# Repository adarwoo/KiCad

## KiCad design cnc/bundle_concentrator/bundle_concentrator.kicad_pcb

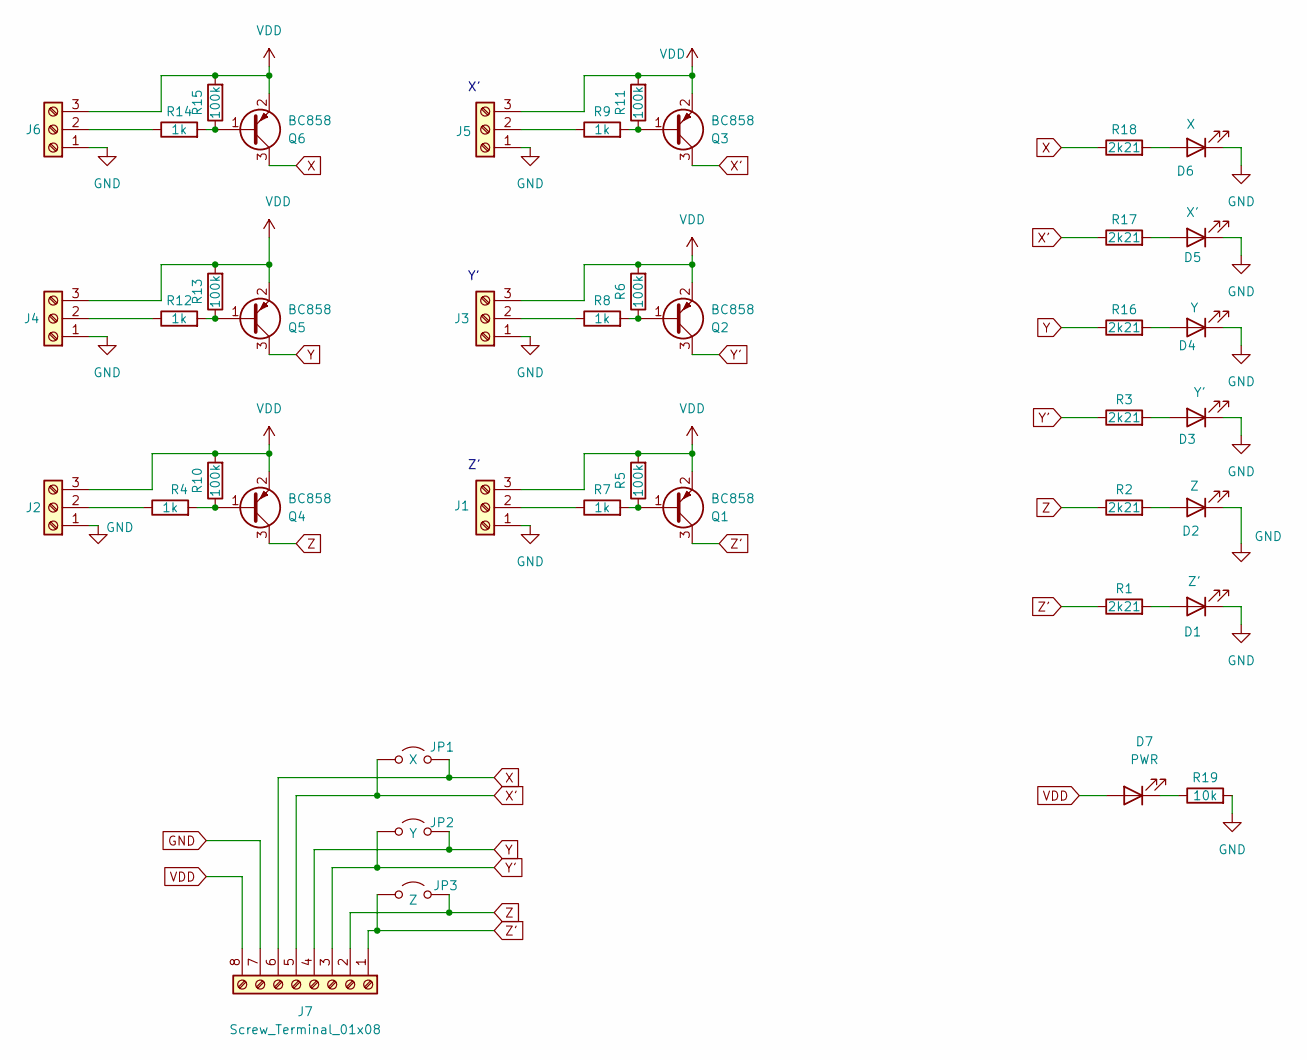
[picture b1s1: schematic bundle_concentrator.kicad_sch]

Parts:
D1: Z'; LED_D3.0mm
D2: Z; LED_D3.0mm
D3: Y'; LED_D3.0mm
D4: Y; LED_D3.0mm
D5: X'; LED_D3.0mm
D6: X; LED_D3.0mm
D7: PWR; LED_D3.0mm
J1: Z'; PhoenixContact_MCV_1,5_3-G-3.5_1x03_P3.50mm_Vertical
J2: Z; PhoenixContact_MCV_1,5_3-G-3.5_1x03_P3.50mm_Vertical
J3: Y'; PhoenixContact_MCV_1,5_3-G-3.5_1x03_P3.50mm_Vertical
J4: Y; PhoenixContact_MCV_1,5_3-G-3.5_1x03_P3.50mm_Vertical
J5: X'; PhoenixContact_MCV_1,5_3-G-3.5_1x03_P3.50mm_Vertical
J6: XX; PhoenixContact_MCV_1,5_3-G-3.5_1x03_P3.50mm_Vertical
J7: Screw_Terminal_01x08; PhoenixContact_MCV_1,5_8-G-3.81_1x08_P3.81mm_Vertical
JP1: X; PinHeader_1x02_P2.54mm_Vertical
JP2: Y; PinHeader_1x02_P2.54mm_Vertical
JP3: Z; PinHeader_1x02_P2.54mm_Vertical
Q1, Q2, Q3, Q4, Q5, Q6: BC858; SOT-23
R1, R2, R3, R16, R17, R18: 2k21; R_1206_3216Metric_Pad1.30x1.75mm_HandSolder
R4, R7, R8, R9, R12, R14: 1k; R_1206_3216Metric_Pad1.30x1.75mm_HandSolder
R5, R6, R10, R11, R13, R15: 100k; R_1206_3216Metric_Pad1.30x1.75mm_HandSolder
R19: 10k; R_1206_3216Metric_Pad1.30x1.75mm_HandSolder

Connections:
GND: D1.1 (K), D2.1 (K), D3.1 (K), D4.1 (K), D5.1 (K), D6.1 (K), J1.1, J2.1, J3.1, J4.1, J5.1, J6.1, J7.7, R19.2
unnamed: D1.2 (A), R1.2
unnamed: D2.2 (A), R2.2
unnamed: D3.2 (A), R3.2
unnamed: D4.2 (A), R16.2
unnamed: D5.2 (A), R17.2
unnamed: D6.2 (A), R18.2
unnamed: D7.1 (K), R19.1
unnamed: J1.2, R7.1
unnamed: J2.2, R4.1
unnamed: J3.2, R8.1
unnamed: J4.2, R12.1
unnamed: J5.2, R9.1
unnamed: J6.2, R14.1
unnamed: Q1.1 (B), R5.1, R7.2
unnamed: Q2.1 (B), R6.1, R8.2
unnamed: Q3.1 (B), R9.2, R11.1
unnamed: Q4.1 (B), R4.2, R10.1
unnamed: Q5.1 (B), R12.2, R13.1
unnamed: Q6.1 (B), R14.2, R15.1
VDD: D7.2 (A), J1.3, J2.3, J3.3, J4.3, J5.3, J6.3, J7.8, Q1.2 (E), Q2.2 (E), Q3.2 (E), Q4.2 (E), Q5.2 (E), Q6.2 (E), R5.2, R6.2, R10.2, R11.2, R13.2, R15.2
X: J7.6, JP1.2 (B), Q6.3 (C), R18.1
X': J7.5, JP1.1 (A), Q3.3 (C), R17.1
Y: J7.4, JP2.2 (B), Q5.3 (C), R16.1
Y': J7.3, JP2.1 (A), Q2.3 (C), R3.1
Z: J7.2, JP3.2 (B), Q4.3 (C), R2.1
Z': J7.1, JP3.1 (A), Q1.3 (C), R1.1

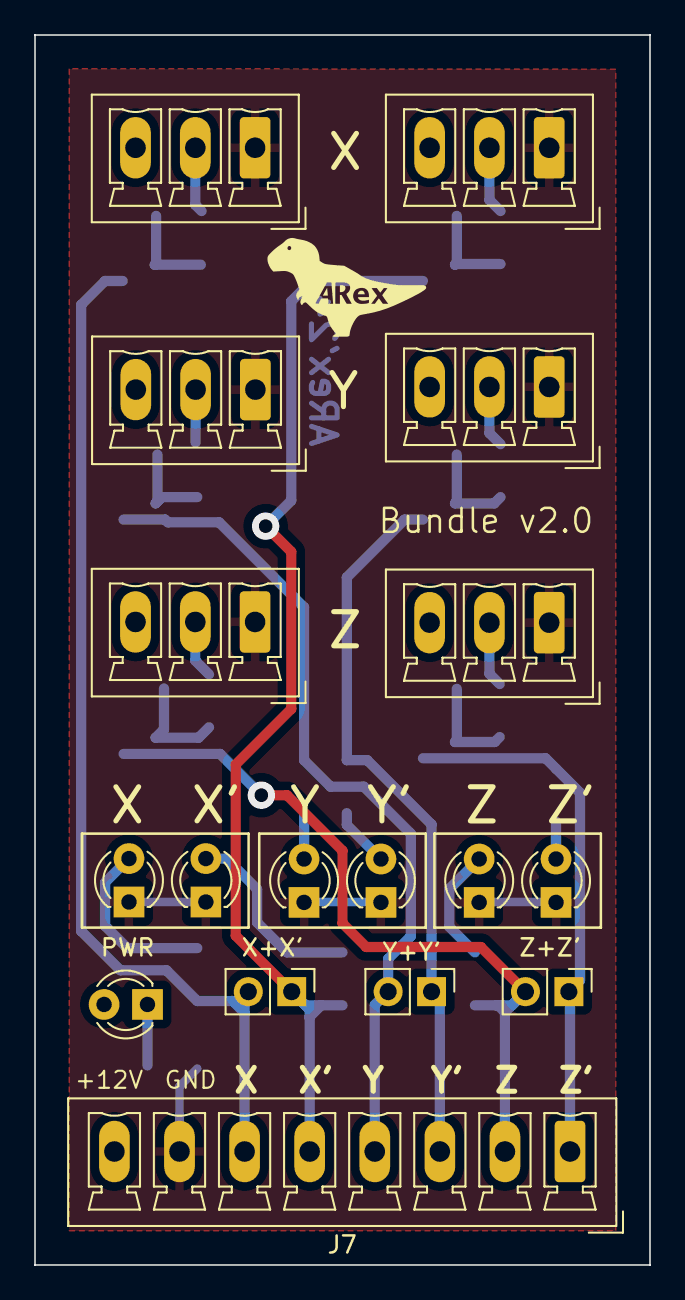
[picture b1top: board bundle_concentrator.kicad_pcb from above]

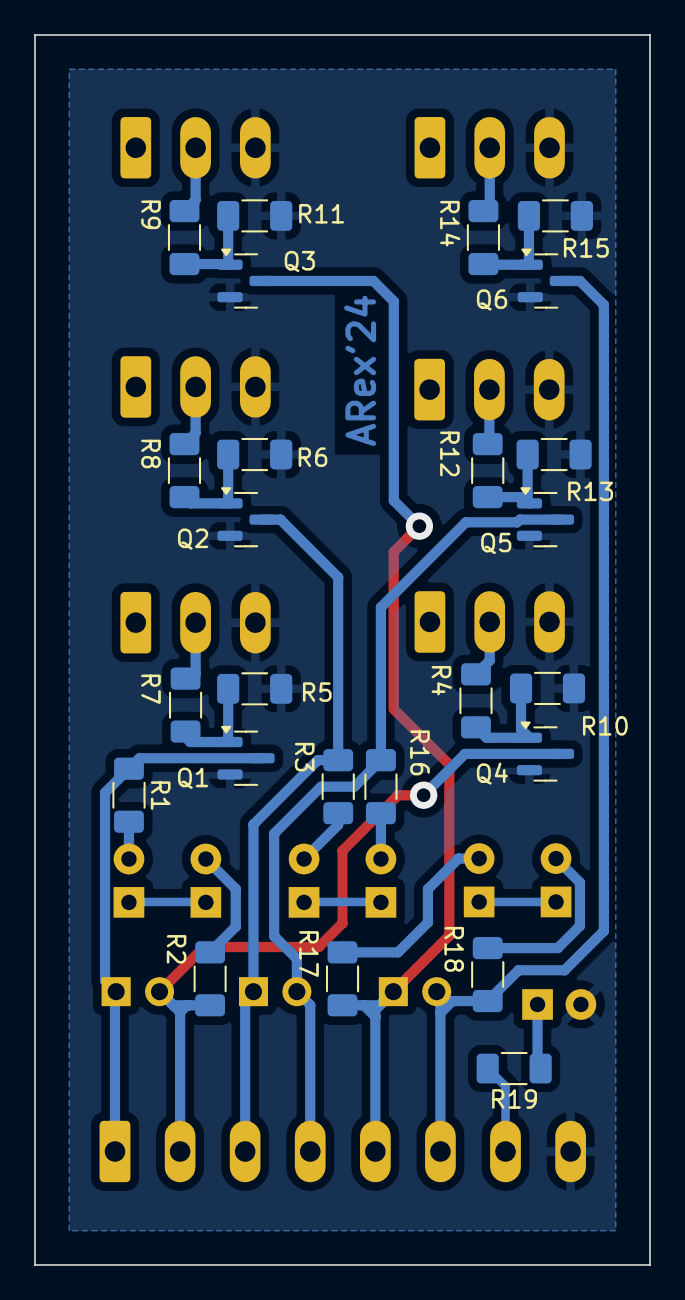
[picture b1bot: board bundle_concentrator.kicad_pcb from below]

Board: 2 copper layers, 36.0 x 72.0 mm, 42 parts (25 on the bottom side), 27 nets.

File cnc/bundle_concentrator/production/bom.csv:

Designator,Footprint,Quantity,Value,LCSC Part #
D1,LED_D3.0mm,1,Z',
D2,LED_D3.0mm,1,Z,
D3,LED_D3.0mm,1,Y',
D4,LED_D3.0mm,1,Y,
D5,LED_D3.0mm,1,X',
D6,LED_D3.0mm,1,X,
D7,LED_D3.0mm,1,PWR,
J1,"PhoenixContact_MCV_1,5_3-G-3.5_1x03_P3.50mm_Vertical",1,Z',
J2,"PhoenixContact_MCV_1,5_3-G-3.5_1x03_P3.50mm_Vertical",1,Z,
J3,"PhoenixContact_MCV_1,5_3-G-3.5_1x03_P3.50mm_Vertical",1,Y',
J4,"PhoenixContact_MCV_1,5_3-G-3.5_1x03_P3.50mm_Vertical",1,Y,
J5,"PhoenixContact_MCV_1,5_3-G-3.5_1x03_P3.50mm_Vertical",1,X',
J6,"PhoenixContact_MCV_1,5_3-G-3.5_1x03_P3.50mm_Vertical",1,XX,
J7,"PhoenixContact_MCV_1,5_8-G-3.81_1x08_P3.81mm_Vertical",1,Screw_Terminal_01x08,
JP1,PinHeader_1x02_P2.54mm_Vertical,1,X,
JP2,PinHeader_1x02_P2.54mm_Vertical,1,Y,
JP3,PinHeader_1x02_P2.54mm_Vertical,1,Z,
"Q1, Q2, Q3, Q4, Q5, Q6",SOT-23,6,BC858,
"R1, R16, R17, R18, R19, R2, R3",1206,7,10k,
"R10, R11, R13, R15, R5, R6",1206,6,100k,
"R12, R14, R4, R7, R8, R9",1206,6,1k,

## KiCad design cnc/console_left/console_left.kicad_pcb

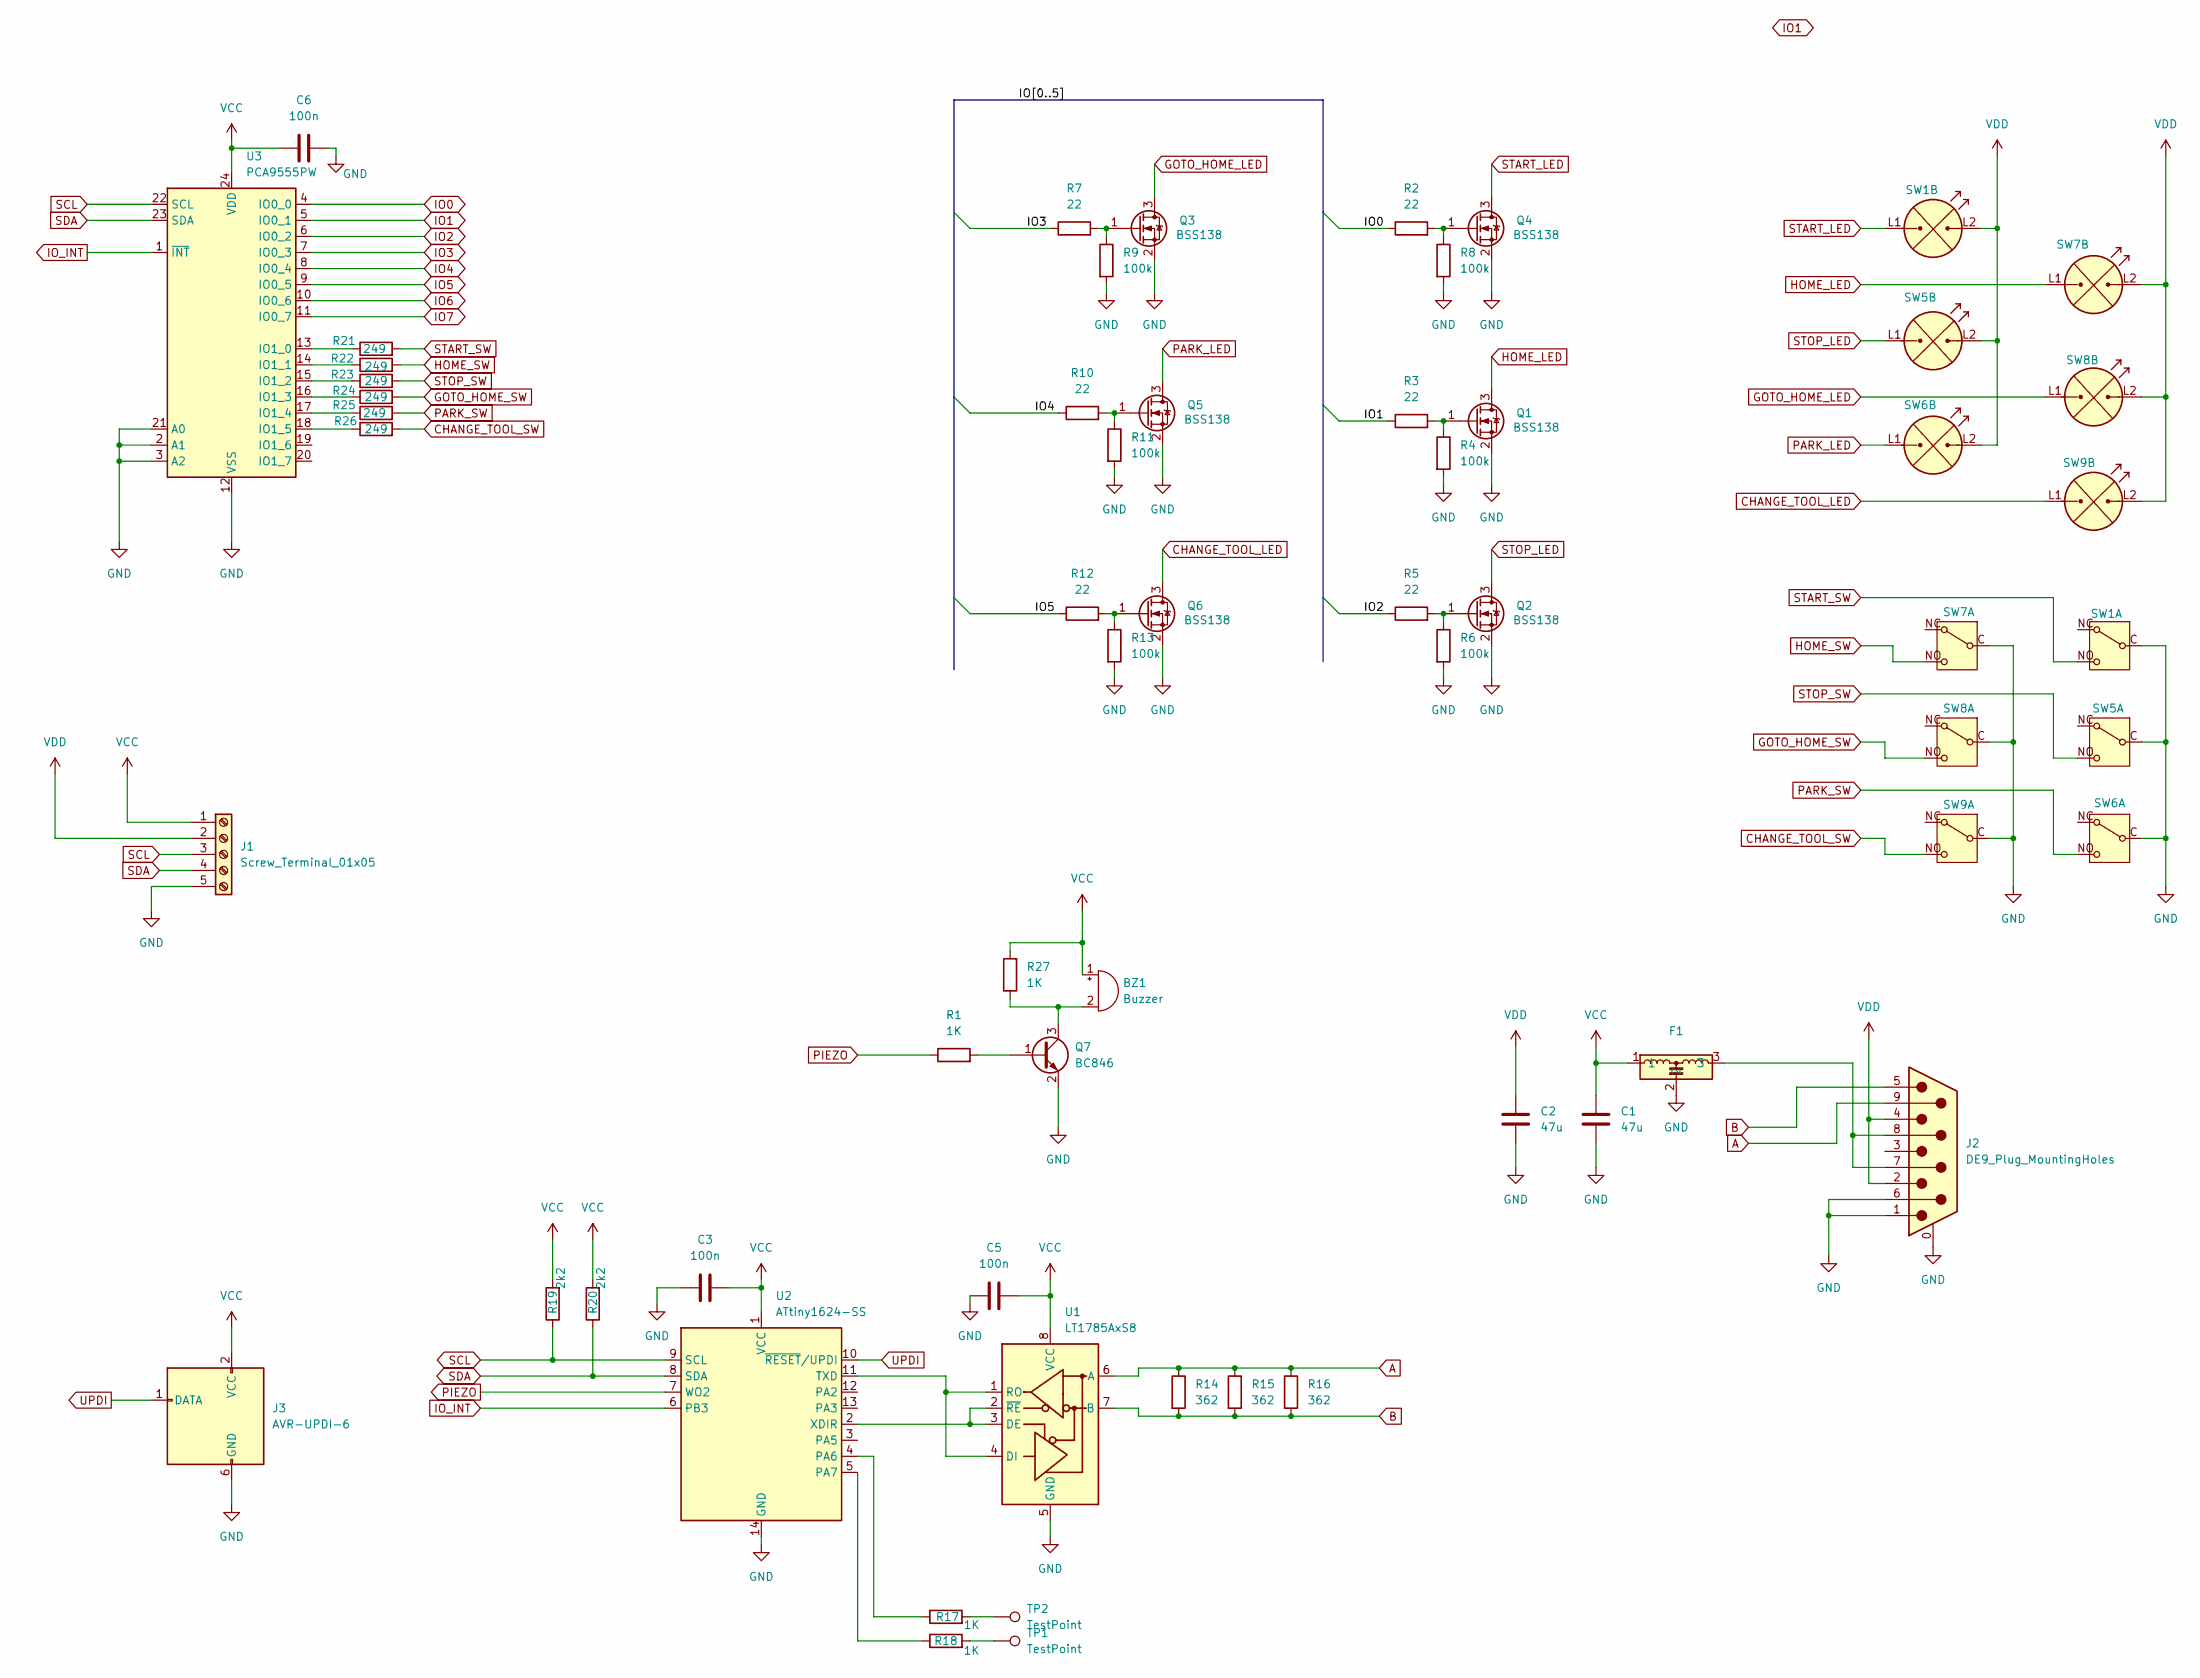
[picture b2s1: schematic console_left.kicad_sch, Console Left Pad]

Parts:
BZ1: Buzzer; Buzzer_Murata_PKLCS1212E
C1, C2: 47u; C_1210_3225Metric_Pad1.33x2.70mm_HandSolder
C3, C5, C6: 100n; C_0603_1608Metric_Pad1.08x0.95mm_HandSolder
F1: Murata_NFM61R
J1: Screw_Terminal_01x05; Molex_KK-254_AE-6410-05A_1x05_P2.54mm_Vertical
J2: DE9_Plug_MountingHoles; DSUB-9_Female_EdgeMount_P2.77mm
J3: AVR-UPDI-6; PinHeader_2x03_P2.54mm_Vertical
Q1, Q2, Q3, Q4, Q5, Q6: BSS138; SOT-23
Q7: BC846; SOT-23
R1, R17, R18, R27: 1K; R_1206_3216Metric_Pad1.30x1.75mm_HandSolder
R2, R3, R5, R7, R10, R12: 22; R_1206_3216Metric_Pad1.30x1.75mm_HandSolder
R4, R6, R8, R9, R11, R13: 100k; R_1206_3216Metric_Pad1.30x1.75mm_HandSolder
R14, R15, R16: 362; R_1206_3216Metric_Pad1.30x1.75mm_HandSolder
R19, R20: 2k2; R_1206_3216Metric_Pad1.30x1.75mm_HandSolder
R21, R22, R23, R24, R25, R26: 249; R_1206_3216Metric_Pad1.30x1.75mm_HandSolder
SW1, SW5, SW6, SW7, SW8, SW9: PUSH_STDP_LED
TP1, TP2: TestPoint; TestPoint_Loop_D1.80mm_Drill1.0mm_Beaded
U1: LT1785AxS8; SOIC-8_3.9x4.9mm_P1.27mm
U2: ATtiny1624-SS; SOIC-14_3.9x8.7mm_P1.27mm
U3: PCA9555PW; TSSOP-24_4.4x7.8mm_P0.65mm

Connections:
A: J2.9, R14.1, R15.1, R16.1, U1.6 (A)
B: J2.5, R14.2, R15.2, R16.2, U1.7 (B)
CHANGE_TOOL_LED: Q6.3 (D), SW9.L1 (AK)
CHANGE_TOOL_SW: R26.2, SW9.NO
GND: C1.2, C2.2, C3.1, C5.1, C6.2, F1.2, J1.5, J2.0 (PAD), J2.1, J2.6, J3.6 (GND), Q1.2 (S), Q2.2 (S), Q3.2 (S), Q4.2 (S), Q5.2 (S), Q6.2 (S), Q7.2 (E), R4.2, R6.2, R8.2, R9.2, R11.2, R13.2, SW1.C, SW5.C, SW6.C, SW7.C, SW8.C, SW9.C, U1.5 (GND), U2.14 (GND), U3.2 (A1), U3.3 (A2), U3.12 (VSS), U3.21 (A0)
GOTO_HOME_LED: Q3.3 (D), SW8.L1 (AK)
GOTO_HOME_SW: R24.2, SW8.NO
HOME_LED: Q1.3 (D), SW7.L1 (AK)
HOME_SW: R22.2, SW7.NO
IO0: R2.1, U3.4 (IO0_0)
IO1: R3.1, U3.5 (IO0_1)
IO2: R5.1, U3.6 (IO0_2)
IO3: R7.1, U3.7 (IO0_3)
IO4: R10.1, U3.8 (IO0_4)
IO5: R12.1, U3.9 (IO0_5)
IO6: U3.10 (IO0_6)
IO7: U3.11 (IO0_7)
IO_INT: U2.6 (PB3), U3.1 (~INT)
unnamed: BZ1.2 (-), Q7.3 (C), R27.1
unnamed: F1.3, J2.7, J2.8
unnamed: Q1.1 (G), R3.2, R4.1
unnamed: Q2.1 (G), R5.2, R6.1
unnamed: Q3.1 (G), R7.2, R9.1
unnamed: Q4.1 (G), R2.2, R8.1
unnamed: Q5.1 (G), R10.2, R11.1
unnamed: Q6.1 (G), R12.2, R13.1
unnamed: Q7.1 (B), R1.2
unnamed: R17.2, TP2.1
unnamed: R18.2, TP1.1
unnamed: U1.2 (~RE), U1.3 (DE), U2.2 (XDIR)
unnamed: U1.1 (RO), U1.4 (DI), U2.11 (TXD)
unnamed: R17.1, U2.4 (PA6)
unnamed: R18.1, U2.5 (PA7)
unnamed: R21.1, U3.13 (IO1_0)
unnamed: R22.1, U3.14 (IO1_1)
unnamed: R23.1, U3.15 (IO1_2)
unnamed: R24.1, U3.16 (IO1_3)
unnamed: R25.1, U3.17 (IO1_4)
unnamed: R26.1, U3.18 (IO1_5)
PARK_LED: Q5.3 (D), SW6.L1 (AK)
PARK_SW: R25.2, SW6.NO
PIEZO: R1.1, U2.7 (WO2)
SCL: J1.3, R19.1, U2.9 (SCL), U3.22 (SCL)
SDA: J1.4, R20.1, U2.8 (SDA), U3.23 (SDA)
START_LED: Q4.3 (D), SW1.L1 (AK)
START_SW: R21.2, SW1.NO
STOP_LED: Q2.3 (D), SW5.L1 (AK)
STOP_SW: R23.2, SW5.NO
UPDI: J3.1 (DATA), U2.10 (~RESET/UPDI)
VCC: BZ1.1 (+), C1.1, C3.2, C5.2, C6.1, F1.1, J1.1, J3.2 (VCC), R19.2, R20.2, R27.2, U1.8 (VCC), U2.1 (VCC), U3.24 (VDD)
VDD: C2.1, J1.2, J2.2, J2.4, SW1.L2 (KA), SW5.L2 (KA), SW6.L2 (KA), SW7.L2 (KA), SW8.L2 (KA), SW9.L2 (KA)

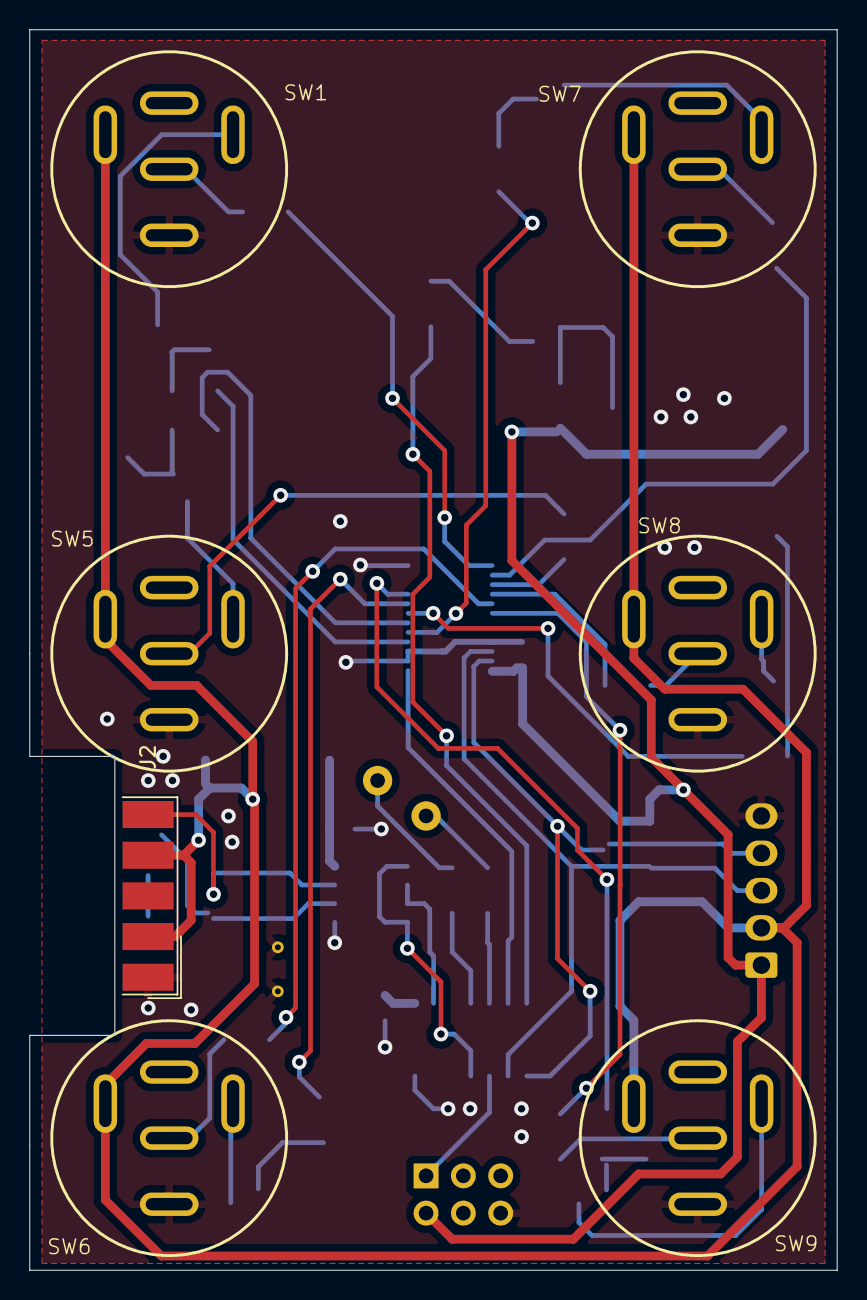
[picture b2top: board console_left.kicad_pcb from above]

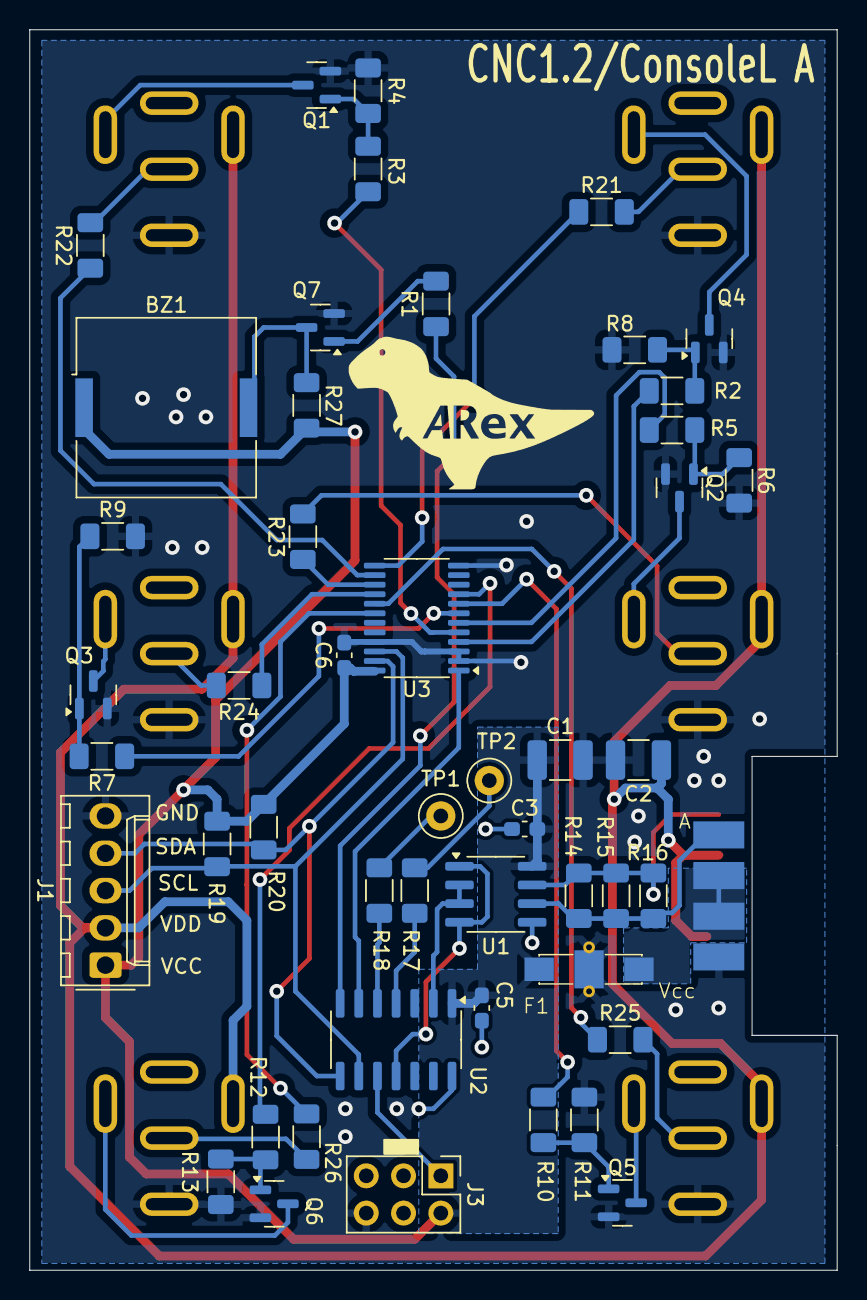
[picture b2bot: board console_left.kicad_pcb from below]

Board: 2 copper layers, 55.0 x 84.5 mm, 55 parts (48 on the bottom side), 49 nets.

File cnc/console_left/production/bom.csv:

Designator,Footprint,Quantity,Value,LCSC Part #
BZ1,Buzzer_Murata_PKLCS1212E,1,Buzzer,
"C1, C2",1210,2,47u,
"C3, C5, C6",0603,3,100n,
F1,Murata_NFM61R,1,~,
J1,Molex_KK-254_AE-6410-05A_1x05_P2.54mm_Vertical,1,Screw_Terminal_01x05,
J2,DSUB-9_Female_EdgeMount_P2.77mm,1,DE9_Plug_MountingHoles,
J3,PinHeader_2x03_P2.54mm_Vertical,1,AVR-UPDI-6,
"Q1, Q2, Q3, Q4, Q5, Q6",SOT-23,6,BSS138,
Q7,SOT-23,1,BC846,
"R1, R17, R18, R27",1206,4,1K,
"R10, R12, R2, R3, R5, R7",1206,6,22,
"R11, R13, R4, R6, R8, R9",1206,6,100k,
"R14, R15, R16",1206,3,362,
"R19, R20",1206,2,2k2,
"R21, R22, R23, R24, R25, R26",1206,6,332,
"SW1, SW5, SW6, SW7, SW8, SW9",PUSH_STDP_LED,6,~,
"TP1, TP2",TestPoint_Loop_D1.80mm_Drill1.0mm_Beaded,2,TestPoint,
U1,SOIC-8_3.9x4.9mm_P1.27mm,1,LT1785AxS8,
U2,SOIC-14_3.9x8.7mm_P1.27mm,1,ATtiny1624-SS,
U3,TSSOP-24_4.4x7.8mm_P0.65mm,1,PCA9555PW,

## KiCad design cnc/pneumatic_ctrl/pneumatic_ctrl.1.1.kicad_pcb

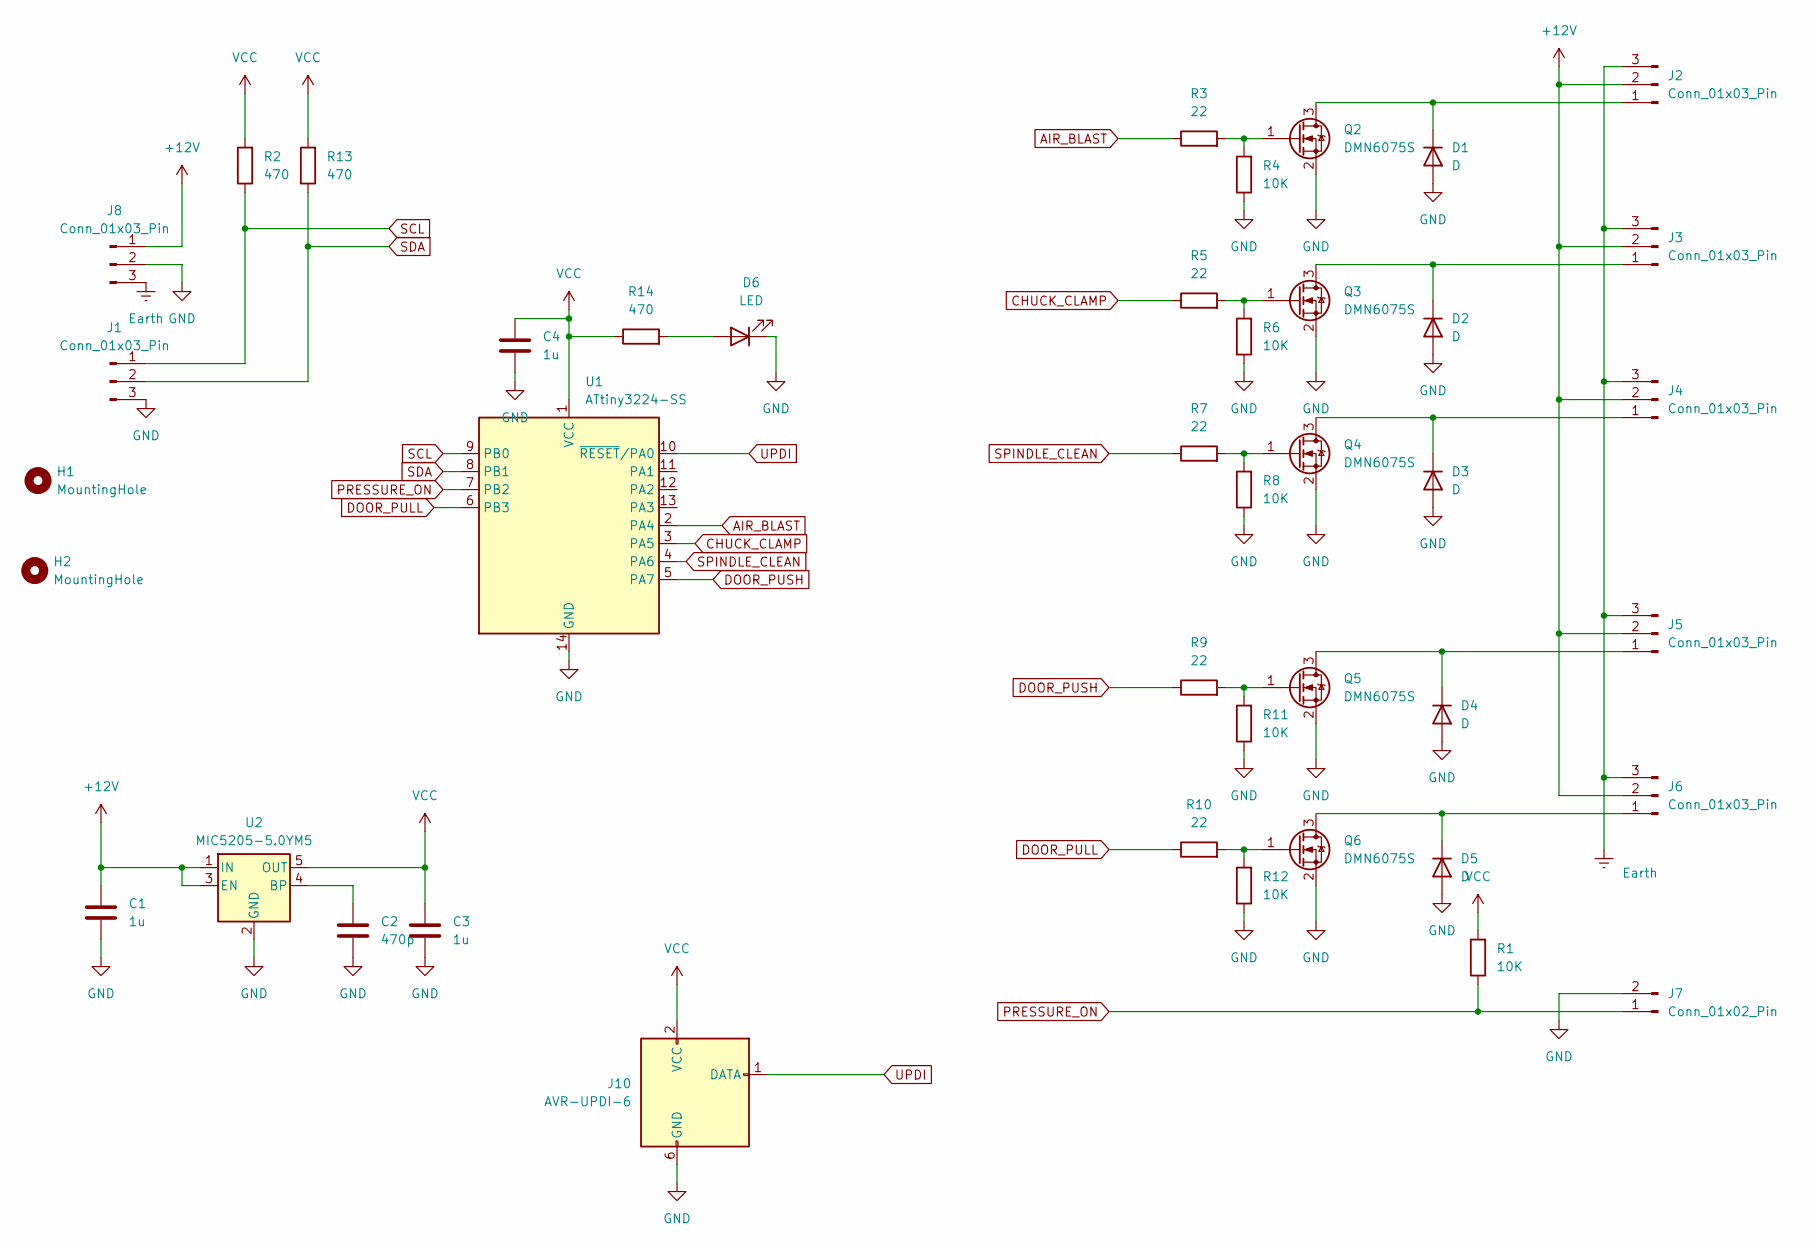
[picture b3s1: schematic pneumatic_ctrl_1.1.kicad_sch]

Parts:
C1, C3, C4: 1u; C_1206_3216Metric_Pad1.33x1.80mm_HandSolder
C2: 470p; C_0805_2012Metric_Pad1.18x1.45mm_HandSolder
D1, D2, D3, D4, D5: D; D_MicroSMP_AK
D6: LED; LED_D3.0mm
H1, H2: MountingHole; MountingHole_3.2mm_M3_DIN965
J1, J2, J3, J4, J5, J6, J8: Conn_01x03_Pin; PhoenixContact_MCV_1,5_3-G-3.81_1x03_P3.81mm_Vertical
J7: Conn_01x02_Pin; PhoenixContact_MCV_1,5_2-G-3.81_1x02_P3.81mm_Vertical
J10: AVR-UPDI-6; PinHeader_2x03_P2.54mm_Vertical
Q2, Q3, Q4, Q5, Q6: DMN6075S; SOT-23
R1, R4, R6, R8, R11, R12: 10K; R_1206_3216Metric_Pad1.30x1.75mm_HandSolder
R2, R13, R14: 470; R_1206_3216Metric_Pad1.30x1.75mm_HandSolder
R3, R5, R7, R9, R10: 22; R_1206_3216Metric_Pad1.30x1.75mm_HandSolder
U1: ATtiny3224-SS; SOIC-14_3.9x8.7mm_P1.27mm
U2: MIC5205-5.0YM5; SOT-23-5

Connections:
+12V: C1.1, J2.2, J3.2, J4.2, J5.2, J6.2, J8.1, U2.1 (IN), U2.3 (EN)
AIR_BLAST: R3.1, U1.2 (PA4)
CHUCK_CLAMP: R5.1, U1.3 (PA5)
DOOR_PULL: R10.1, U1.6 (PB3)
DOOR_PUSH: R9.1, U1.5 (PA7)
Earth: J2.3, J3.3, J4.3, J5.3, J6.3, J8.3
GND: C1.2, C2.2, C3.2, C4.2, D1.2 (A), D2.2 (A), D3.2 (A), D4.2 (A), D5.2 (A), D6.1 (K), J1.3, J7.2, J8.2, J10.6 (GND), Q2.2 (S), Q3.2 (S), Q4.2 (S), Q5.2 (S), Q6.2 (S), R4.1, R6.1, R8.1, R11.1, R12.1, U1.14 (GND), U2.2 (GND)
unnamed: D1.1 (K), J2.1, Q2.3 (D)
unnamed: D2.1 (K), J3.1, Q3.3 (D)
unnamed: D3.1 (K), J4.1, Q4.3 (D)
unnamed: D4.1 (K), J5.1, Q5.3 (D)
unnamed: D5.1 (K), J6.1, Q6.3 (D)
unnamed: D6.2 (A), R14.2
unnamed: Q2.1 (G), R3.2, R4.2
unnamed: Q3.1 (G), R5.2, R6.2
unnamed: Q4.1 (G), R7.2, R8.2
unnamed: Q5.1 (G), R9.2, R11.2
unnamed: Q6.1 (G), R10.2, R12.2
unnamed: C2.1, U2.4 (BP)
PRESSURE_ON: J7.1, R1.1, U1.7 (PB2)
SCL: J1.1, R2.1, U1.9 (PB0)
SDA: J1.2, R13.1, U1.8 (PB1)
SPINDLE_CLEAN: R7.1, U1.4 (PA6)
UPDI: J10.1 (DATA), U1.10 (~RESET/PA0)
VCC: C3.1, C4.1, J10.2 (VCC), R1.2, R2.2, R13.2, R14.1, U1.1 (VCC), U2.5 (OUT)

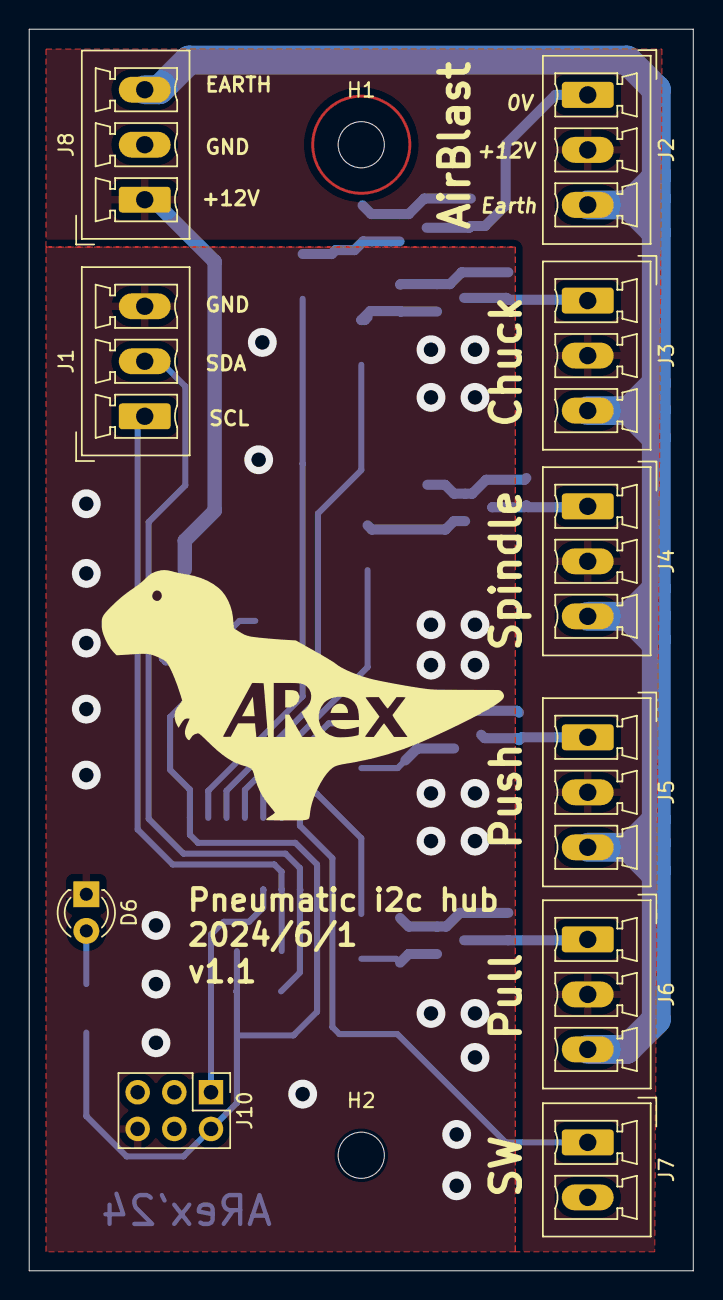
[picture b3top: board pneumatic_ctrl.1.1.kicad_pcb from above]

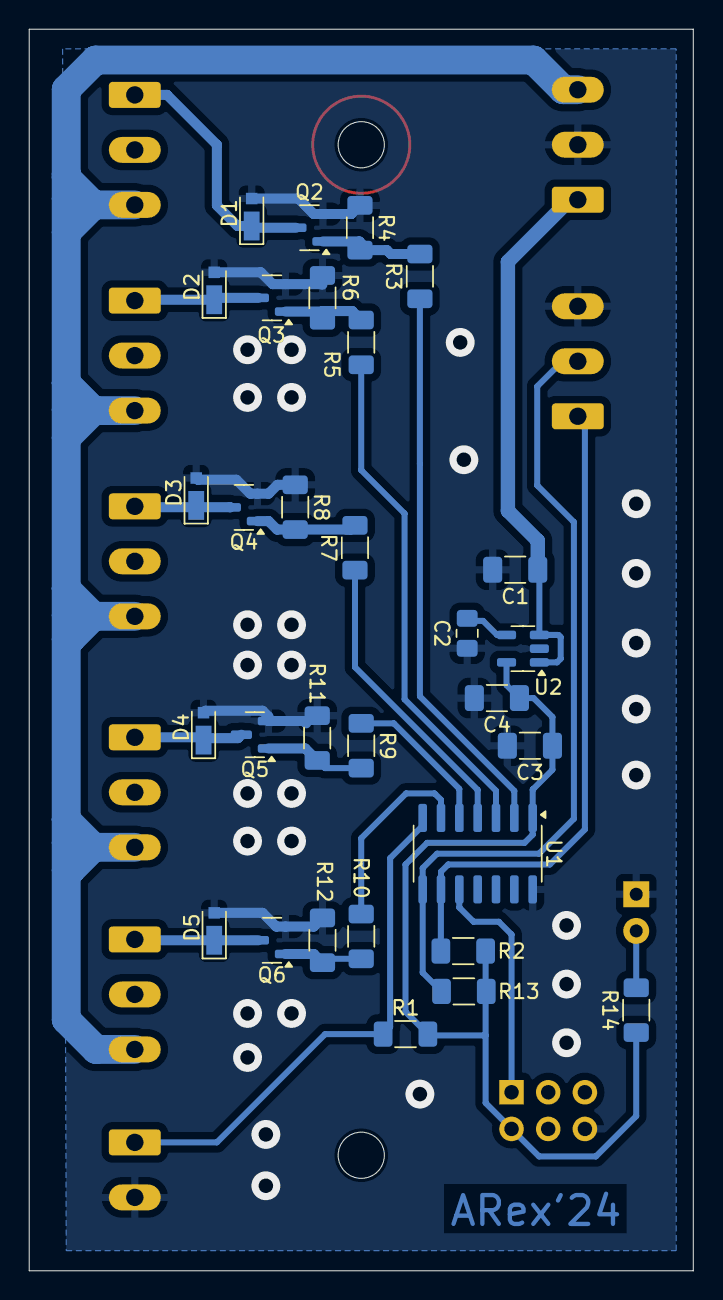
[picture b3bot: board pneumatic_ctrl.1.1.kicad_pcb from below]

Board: 2 copper layers, 46.0 x 86.0 mm, 42 parts (30 on the bottom side), 25 nets.

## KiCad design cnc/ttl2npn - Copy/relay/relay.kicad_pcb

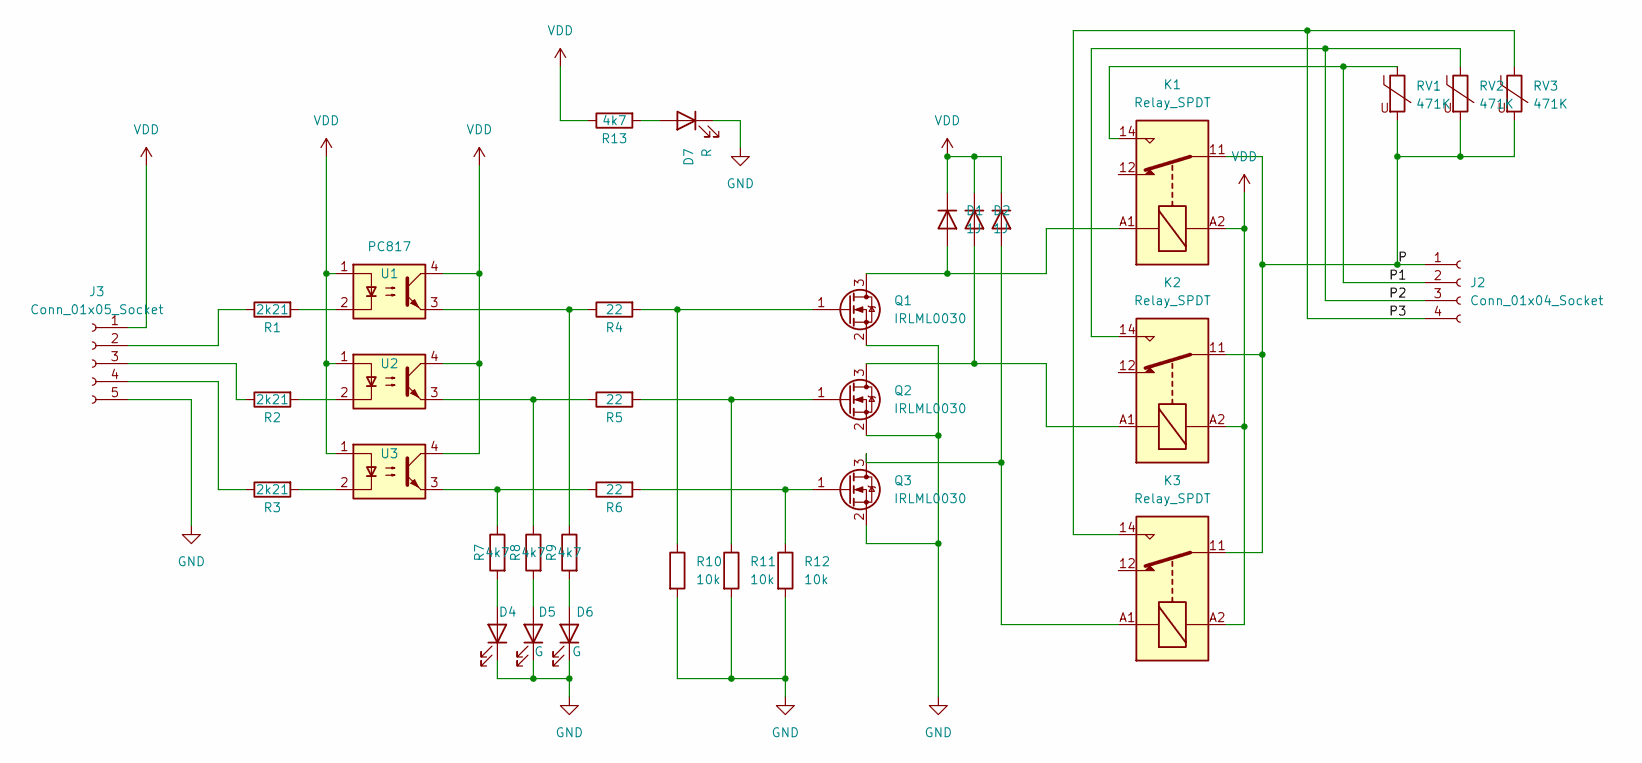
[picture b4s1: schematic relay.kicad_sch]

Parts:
D1, D2, D3: 1J; D_SMA
D4, D5, D6: G; LED_D3.0mm
D7: R; LED_D3.0mm
J2: Conn_01x04_Socket; TerminalBlock_Phoenix_MKDS-1,5-4_1x04_P5.00mm_Horizontal
J3: Conn_01x05_Socket; PhoenixContact_MCV_1,5_5-G-3.81_1x05_P3.81mm_Vertical
K1, K2, K3: Relay_SPDT; Relay_SPDT_Omron_G2RL-1-E
Q1, Q2, Q3: IRLML0030; SOT-23
R1, R2, R3: 2k21; R_1206_3216Metric_Pad1.30x1.75mm_HandSolder
R4, R5, R6: 22; R_1206_3216Metric_Pad1.30x1.75mm_HandSolder
R7, R8, R9, R13: 4k7; R_1206_3216Metric_Pad1.30x1.75mm_HandSolder
R10, R11, R12: 10k; R_1206_3216Metric_Pad1.30x1.75mm_HandSolder
RV1, RV2, RV3: 471K; RV_Disc_D9mm_W3.3mm_P5mm
U1, U2, U3: PC817; DIP-4_W7.62mm

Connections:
/P: J2.1, K1.11, K2.11, K3.11, RV1.2, RV2.2, RV3.2
/P1: J2.2, K1.14, RV1.1
/P2: J2.3, K2.14, RV2.1
/P3: J2.4, K3.14, RV3.1
GND: D4.1 (K), D5.1 (K), D6.1 (K), D7.1 (K), J3.5, Q1.2 (S), Q2.2 (S), Q3.2 (S), R10.2, R11.2, R12.2
unnamed: D1.2 (A), K1.A1, Q1.3 (D)
unnamed: D2.2 (A), K2.A1, Q2.3 (D)
unnamed: D3.2 (A), K3.A1, Q3.3 (D)
unnamed: D4.2 (A), R7.2
unnamed: D5.2 (A), R8.2
unnamed: D6.2 (A), R9.2
unnamed: D7.2 (A), R13.2
unnamed: J3.2, R1.1
unnamed: J3.3, R2.1
unnamed: J3.4, R3.1
unnamed: Q1.1 (G), R4.2, R10.1
unnamed: Q2.1 (G), R5.2, R11.1
unnamed: Q3.1 (G), R6.2, R12.1
unnamed: R1.2, U1.2
unnamed: R2.2, U2.2
unnamed: R3.2, U3.2
unnamed: R4.1, R9.1, U1.3
unnamed: R5.1, R8.1, U2.3
unnamed: R6.1, R7.1, U3.3
VDD: D1.1 (K), D2.1 (K), D3.1 (K), J3.1, K1.A2, K2.A2, K3.A2, R13.1, U1.1, U1.4, U2.1, U2.4, U3.1, U3.4
